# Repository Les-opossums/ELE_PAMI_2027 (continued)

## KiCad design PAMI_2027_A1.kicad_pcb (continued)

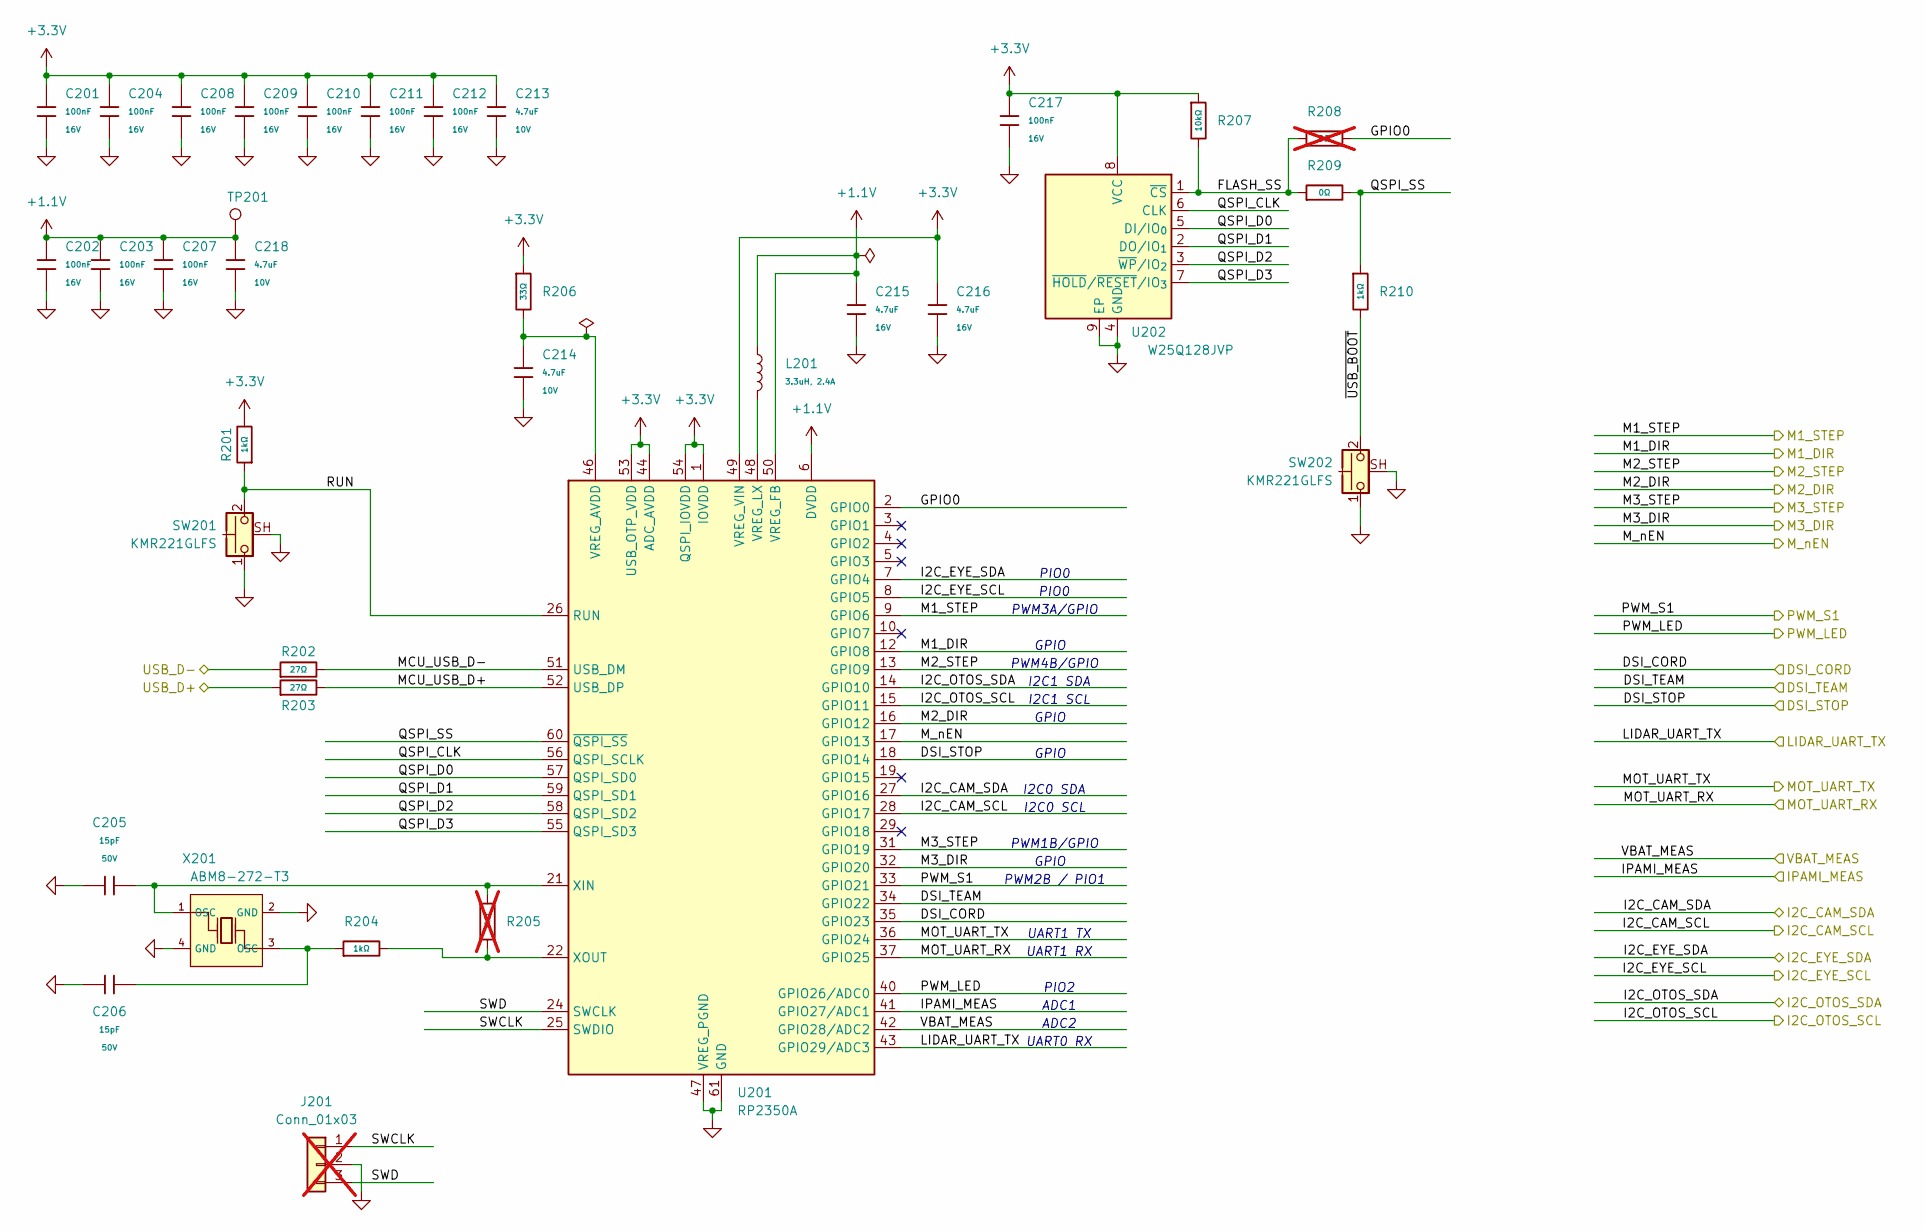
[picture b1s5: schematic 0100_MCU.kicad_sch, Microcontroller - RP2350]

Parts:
C201, C202, C203, C204, C207, C208, C209, C210, C211, C212, C217: 100nF; C_0402; Voltage Rated 16V; Tolerance ±10%; Part CL05B104KO5NNNC; LCSC C1525
C205, C206: 15pF; C_0402; Voltage Rated 50V; Tolerance ±5%; Part 0402CG150J500NT; LCSC C1548
C213, C214, C218: 4.7uF; C_0402; Voltage Rated 10V; Tolerance ±20%; Part CL05A475MP5NRNC; LCSC C23733
C215, C216: 4.7uF; C_0603; Voltage Rated 16V; Tolerance ±10%; Part CL10A475KO8NNNC; LCSC C19666
J201: Conn_01x03; PinHeader_1x03_P2.54mm_Vertical; not fitted
L201: 3.3uH, 2.4A; L_Changjiang_FTC201612S; Part FTC201612S3R3MBCD; LCSC C53281610
R201, R204, R210: 1kΩ; R_0402; Overload Voltage (Max) 50V; Tolerance ±1%; Part 0402WGF1001TCE; LCSC C11702
R202, R203: 27Ω; R_0402; Overload Voltage (Max) 50V; Tolerance ±1%; Part 0402WGF270JTCE; LCSC C25100
R205: 1kΩ; R_0603; Overload Voltage (Max) 75V; Tolerance ±1%; Part 0603WAF1001T5E; LCSC C21190; not fitted
R206: 33Ω; R_0402; Overload Voltage (Max) 50V; Tolerance ±1%; Part 0402WGF330JTCE; LCSC C25105
R207: 10kΩ; R_0402; Overload Voltage (Max) 50V; Tolerance ±1%; Part 0402WGF1002TCE; LCSC C25744
R208: 0Ω; R_0402; Overload Voltage (Max) 50V; Tolerance ±1%; Part 0402WGF0000TCE; LCSC C17168; not fitted
R209: 0Ω; R_0402; Overload Voltage (Max) 50V; Tolerance ±1%; Part 0402WGF0000TCE; LCSC C17168
SW201, SW202: KMR221GLFS; SW_Push_1P1T-SH_NO_CK_KMR2xxG
TP201: TestPoint; TestPoint_Pad_D1.0mm
U201: RP2350A; QFN-60-1EP_7x7mm_P0.4mm_EP3.4x3.4mm
U202: W25Q128JVP; WSON-8-1EP_6x5mm_P1.27mm_EP3.4x4.3mm
X201: ABM8-272-T3; Crystal_SMD_Abracon_ABM8G-4Pin_3.2x2.5mm; Frequency Tolerance ±10ppm; Part X322512MMB4SI; LCSC C20625731

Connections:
+1.1V: C202.1, C203.1, C207.1, C215.1, C218.1, L201.1, TP201.1 (1_1), U201.6 (DVDD), U201.23 (DVDD), U201.39 (DVDD), U201.50 (VREG_FB)
+3.3V: C201.1, C204.1, C208.1, C209.1, C210.1, C211.1, C212.1, C213.1, C216.1, C217.1, R201.2, R206.1, R207.1, U201.1 (IOVDD), U201.11 (IOVDD), U201.20 (IOVDD), U201.30 (IOVDD), U201.38 (IOVDD), U201.44 (ADC_AVDD), U201.45 (IOVDD), U201.49 (VREG_VIN), U201.53 (USB_OTP_VDD), U201.54 (QSPI_IOVDD), U202.8 (VCC); also elsewhere on the board
/I2C_EYE_SCL: U201.8 (GPIO5); also elsewhere on the board
/I2C_EYE_SDA: U201.7 (GPIO4); also elsewhere on the board
/I2C_OTOS_SCL: U201.15 (GPIO11); also elsewhere on the board
/I2C_OTOS_SDA: U201.14 (GPIO10); also elsewhere on the board
/MCU/DSI_CORD: U201.35 (GPIO23); also elsewhere on the board
/MCU/DSI_TEAM: U201.34 (GPIO22); also elsewhere on the board
/MCU/FLASH_SS: R207.2, R208.1, R209.1, U202.1 (~CS)
/MCU/GPIO0: R208.2, U201.2 (GPIO0)
/MCU/I2C_CAM_SCL: U201.28 (GPIO17); also elsewhere on the board
/MCU/I2C_CAM_SDA: U201.27 (GPIO16); also elsewhere on the board
/MCU/IPAMI_MEAS: U201.41 (GPIO27/ADC1); also elsewhere on the board
/MCU/LIDAR_UART_TX: U201.43 (GPIO29/ADC3); also elsewhere on the board
/MCU/M1_DIR: U201.12 (GPIO8); also elsewhere on the board
/MCU/M1_STEP: U201.9 (GPIO6); also elsewhere on the board
/MCU/M2_DIR: U201.16 (GPIO12); also elsewhere on the board
/MCU/M2_STEP: U201.13 (GPIO9); also elsewhere on the board
/MCU/M3_DIR: U201.32 (GPIO20); also elsewhere on the board
/MCU/M3_STEP: U201.31 (GPIO19); also elsewhere on the board
/MCU/MCU_USB_D+: R203.2, U201.52 (USB_DP)
/MCU/MCU_USB_D-: R202.2, U201.51 (USB_DM)
/MCU/MOT_UART_RX: U201.37 (GPIO25); also elsewhere on the board
/MCU/MOT_UART_TX: U201.36 (GPIO24); also elsewhere on the board
/MCU/PWM_LED: U201.40 (GPIO26/ADC0); also elsewhere on the board
/MCU/PWM_S1: U201.33 (GPIO21); also elsewhere on the board
/MCU/QSPI_CLK: U201.56 (QSPI_SCLK), U202.6 (CLK)
/MCU/QSPI_D0: U201.57 (QSPI_SD0), U202.5 (DI/IO_{0})
/MCU/QSPI_D1: U201.59 (QSPI_SD1), U202.2 (DO/IO_{1})
/MCU/QSPI_D2: U201.58 (QSPI_SD2), U202.3 (~WP/IO_{2})
/MCU/QSPI_D3: U201.55 (QSPI_SD3), U202.7 (~HOLD/~RESET/IO_{3})
/MCU/QSPI_SS: R209.2, R210.1, U201.60 (~QSPI_SS)
/MCU/RUN: R201.1, SW201.2, U201.26 (RUN)
/MCU/SWCLK: J201.1, U201.25 (SWDIO)
/MCU/SWD: J201.3, U201.24 (SWCLK)
/MCU/USB_D+: R203.1; also elsewhere on the board
/MCU/USB_D-: R202.1; also elsewhere on the board
/MCU/VBAT_MEAS: U201.42 (GPIO28/ADC2); also elsewhere on the board
/MCU/~USB_BOOT: R210.2, SW202.2
/M_nEN: U201.17 (GPIO13); also elsewhere on the board
/PAMI_STOP: U201.18 (GPIO14); also elsewhere on the board
GND: C201.2, C202.2, C203.2, C204.2, C205.1, C206.1, C207.2, C208.2, C209.2, C210.2, C211.2, C212.2, C213.2, C214.2, C215.2, C216.2, C217.2, C218.2, J201.2, SW201.1, SW201.SH (B), SW202.1, SW202.SH (B), U201.47 (VREG_PGND), U201.61 (GND), U202.4 (GND), U202.9 (EP), X201.2 (GND), X201.4 (GND); also elsewhere on the board
unnamed: C206.2, R204.1, X201.3 (OSC)
unnamed: C214.1, R206.2, U201.46 (VREG_AVDD)
unnamed: L201.2, U201.48 (VREG_LX)
unnamed: C205.2, R205.1, U201.21 (XIN), X201.1 (OSC)
unnamed: R204.2, R205.2, U201.22 (XOUT)

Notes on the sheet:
PIO0
PWM4B/GPIO
UART1 RX
UART1 TX
UART0 RX
I2C1 SDA
I2C0 SDA
PWM3A/GPIO
PIO2
ADC2
GPIO
I2C1 SCL
I2C0 SCL
ADC1
PWM1B/GPIO
PWM2B / PIO1

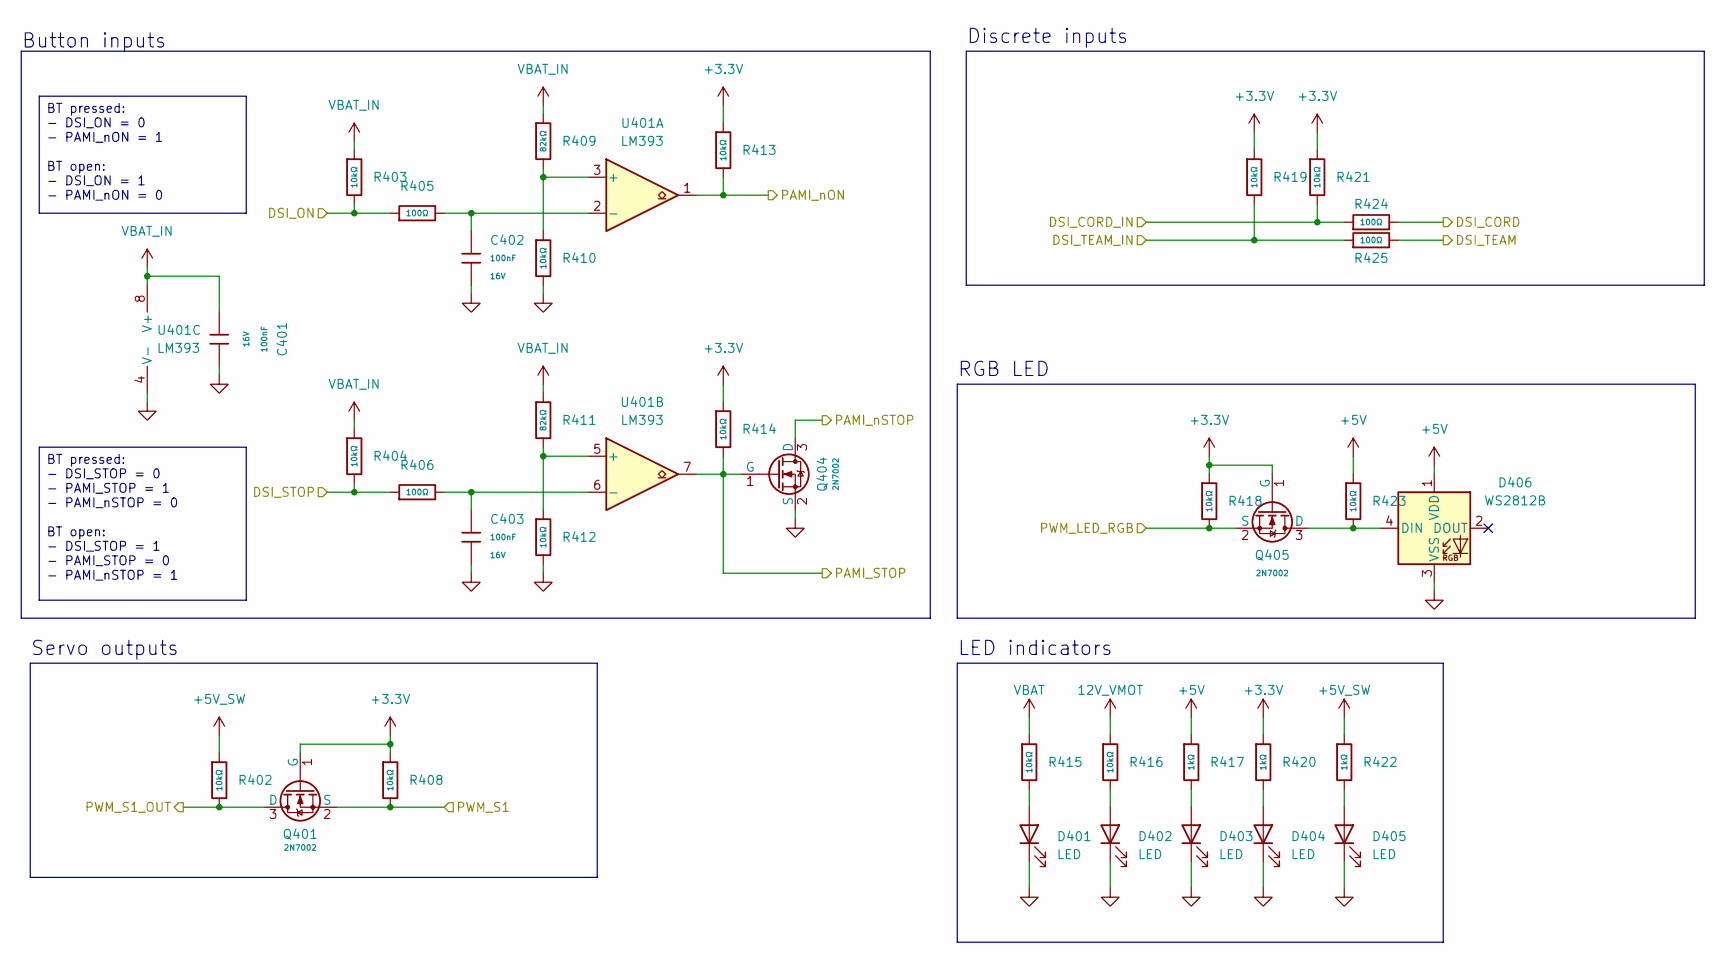
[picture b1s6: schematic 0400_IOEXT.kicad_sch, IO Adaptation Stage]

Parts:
C401, C402, C403: 100nF; C_0402; Voltage Rated 16V; Tolerance ±10%; Part CL05B104KO5NNNC; LCSC C1525
D401, D402, D403, D404, D405: LED; LED_0603_1608Metric
D406: WS2812B; LED_WS2812B_PLCC4_5.0x5.0mm_P3.2mm
Q401, Q404, Q405: 2N7002; Q_SOT-23; Part 2N7002; LCSC C8545
R402, R403, R404, R408, R410, R412, R413, R414, R415, R416, R418, R419, R421, R423: 10kΩ; R_0402; Overload Voltage (Max) 50V; Tolerance ±1%; Part 0402WGF1002TCE; LCSC C25744
R405, R406, R424, R425: 100Ω; R_0402; Overload Voltage (Max) 50V; Tolerance ±1%; Part 0402WGF1000TCE; LCSC C25076
R409, R411: 82kΩ; R_0603; Overload Voltage (Max) 75V; Tolerance ±1%; Part 0603WAF8202T5E; LCSC C23254
R417, R420, R422: 1kΩ; R_0402; Overload Voltage (Max) 50V; Tolerance ±1%; Part 0402WGF1001TCE; LCSC C11702
U401: LM393; SOIC-8_3.9x4.9mm_P1.27mm

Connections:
12V_VMOT: R416.1; also elsewhere on the board
+3.3V: Q401.1 (G), Q405.1 (G), R408.1, R413.1, R414.1, R418.1, R419.1, R420.1, R421.1; also elsewhere on the board
+5V: D406.1 (VDD), R417.1, R423.1; also elsewhere on the board
+5V_SW: R402.1, R422.1; also elsewhere on the board
/IO/DSI_CORD_IN: R421.2, R424.1; also elsewhere on the board
/IO/DSI_ON: R403.2, R405.1; also elsewhere on the board
/IO/DSI_STOP: R404.2, R406.1; also elsewhere on the board
/IO/DSI_TEAM_IN: R419.2, R425.1; also elsewhere on the board
/IO/PWM_S1_OUT: Q401.3 (D), R402.2; also elsewhere on the board
/MCU/DSI_CORD: R424.2; also elsewhere on the board
/MCU/DSI_TEAM: R425.2; also elsewhere on the board
/MCU/PWM_LED: Q405.2 (S), R418.2; also elsewhere on the board
/MCU/PWM_S1: Q401.2 (S), R408.2; also elsewhere on the board
/PAMI_STOP: Q404.1 (G), R414.2, U401.7; also elsewhere on the board
/PAMI_nON: R413.2, U401.1; also elsewhere on the board
/PAMI_nSTOP: Q404.3 (D); also elsewhere on the board
GND: C401.2, C402.1, C403.1, D401.1 (K), D402.1 (K), D403.1 (K), D404.1 (K), D405.1 (K), D406.3 (VSS), Q404.2 (S), R410.2, R412.2, U401.4 (V-); also elsewhere on the board
unnamed: D401.2 (A), R415.2
unnamed: D402.2 (A), R416.2
unnamed: D403.2 (A), R417.2
unnamed: D404.2 (A), R420.2
unnamed: D405.2 (A), R422.2
unnamed: D406.4 (DIN), Q405.3 (D), R423.2
unnamed: R409.2, R410.1, U401.3 (+)
unnamed: C402.2, R405.2, U401.2 (-)
unnamed: R411.2, R412.1, U401.5 (+)
unnamed: C403.2, R406.2, U401.6 (-)
VBAT: R415.1; also elsewhere on the board
VBAT_IN: C401.1, R403.1, R404.1, R409.1, R411.1, U401.8 (V+); also elsewhere on the board

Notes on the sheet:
LED indicators
Discrete inputs
RGB LED
Button inputs
Servo outputs
BT pressed: - DSI_STOP = 0 - PAMI_STOP = 1 - PAMI_nSTOP = 0 BT open: - DSI_STOP = 1 - PAMI_STOP = 0 - PAMI_nSTOP = 1
BT pressed: - DSI_ON = 0 - PAMI_nON = 1 BT open: - DSI_ON = 1 - PAMI_nON = 0

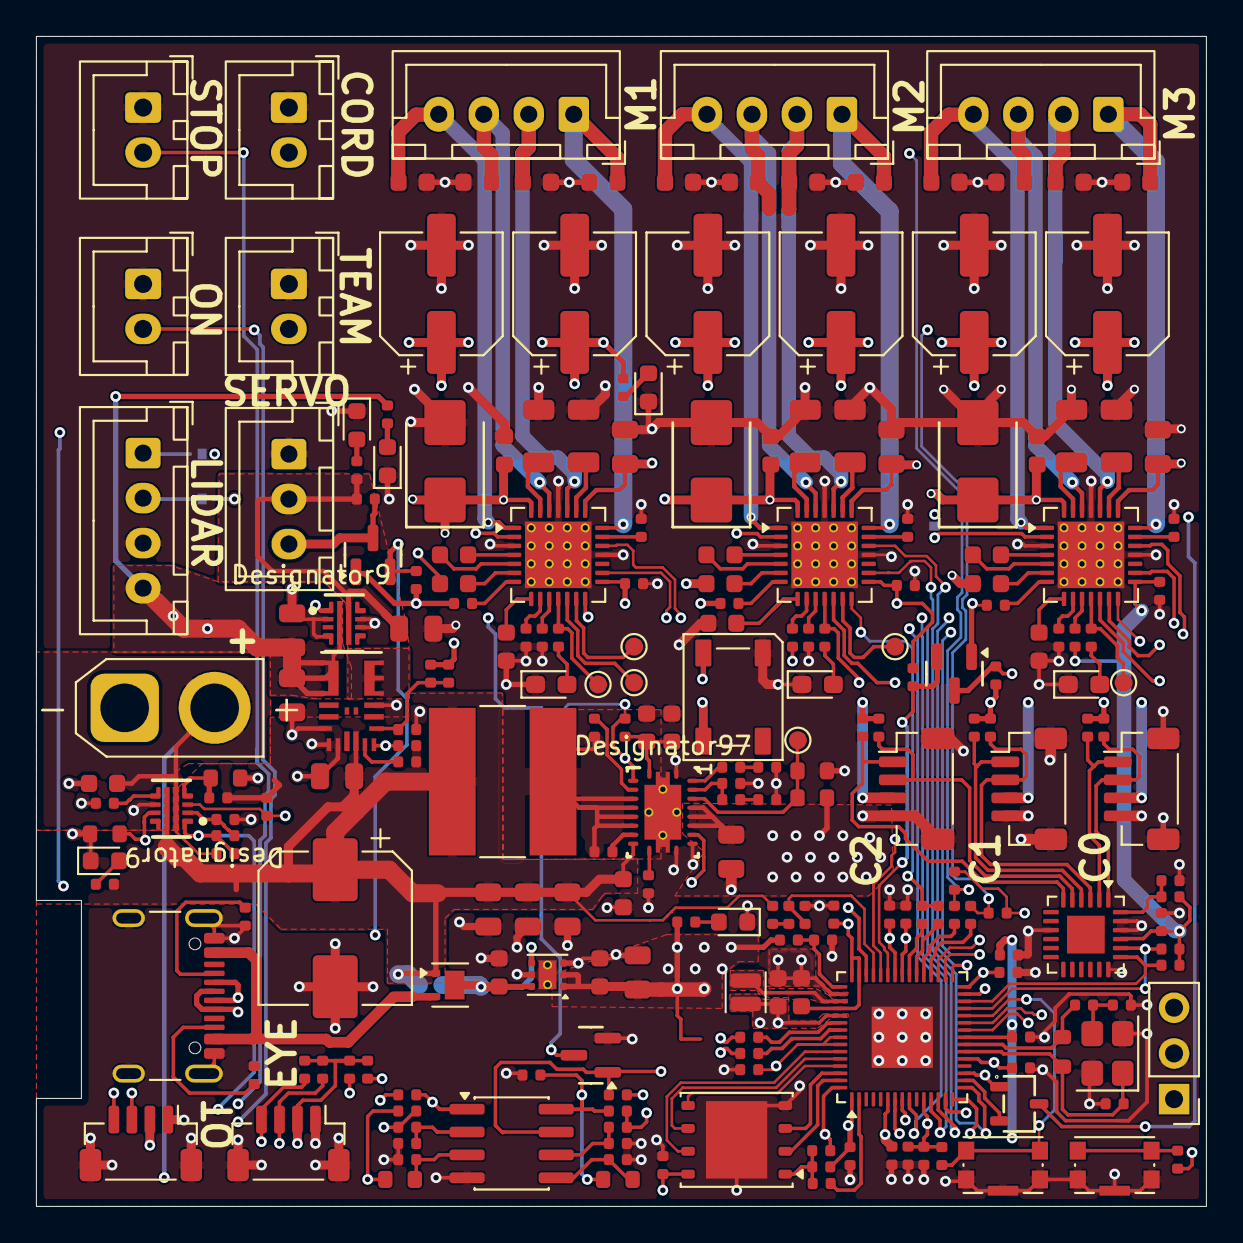
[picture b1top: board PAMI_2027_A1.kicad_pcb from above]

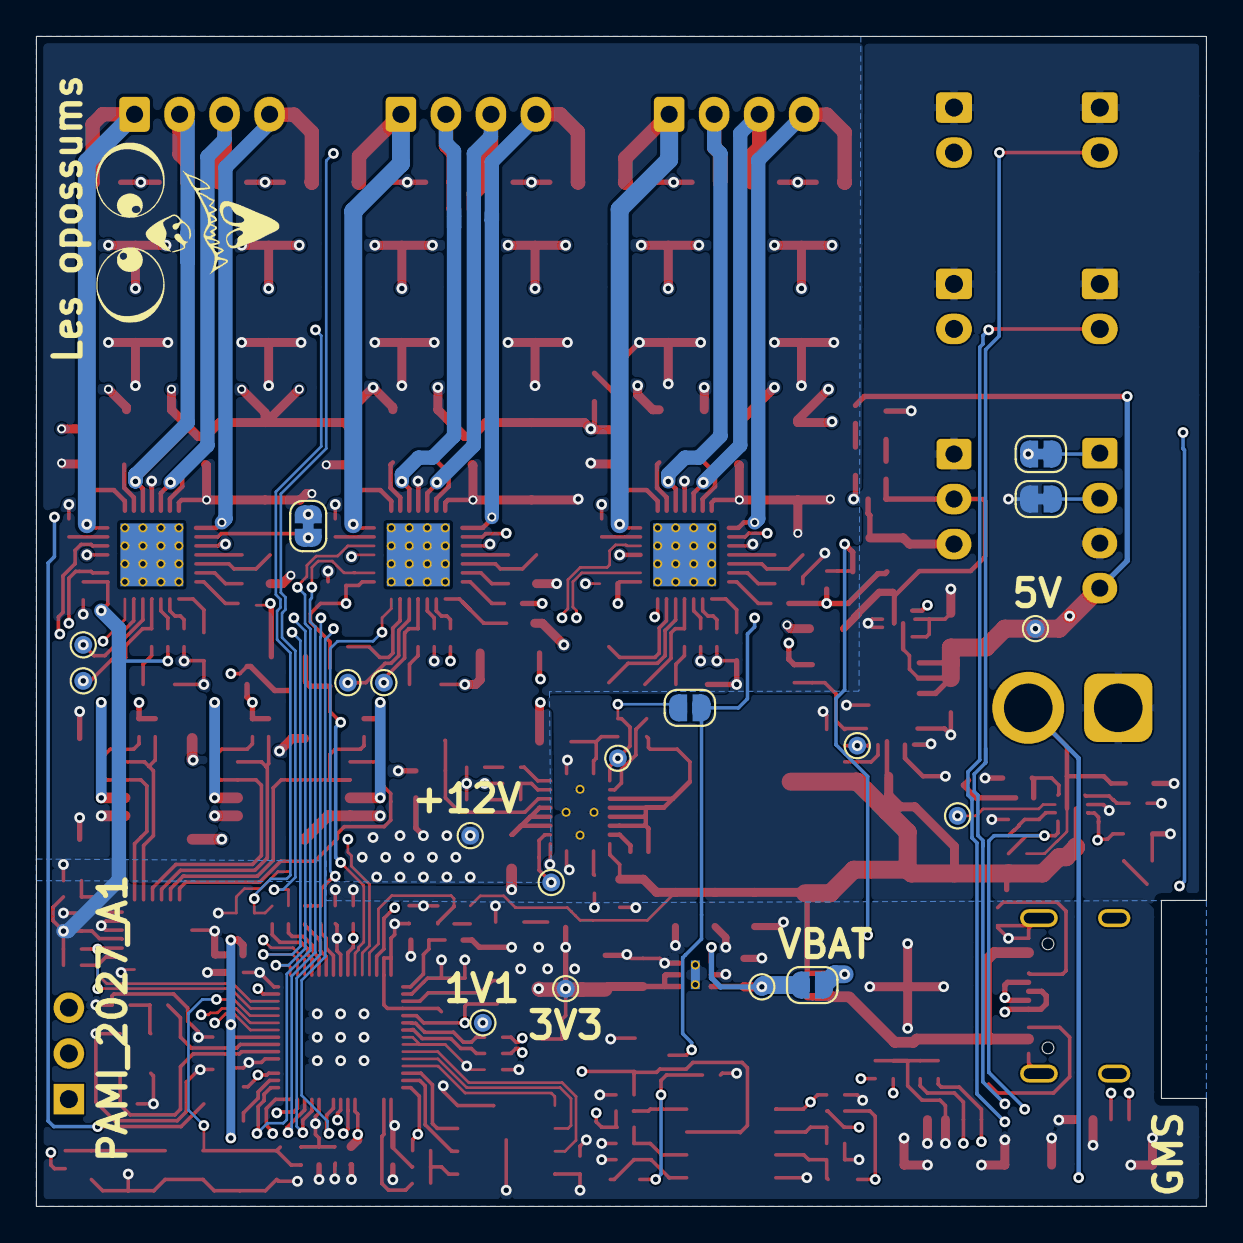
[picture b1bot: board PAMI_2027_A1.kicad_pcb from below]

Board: 4 copper layers, 65.0 x 65.0 mm, 248 parts (18 on the bottom side), 160 nets.
